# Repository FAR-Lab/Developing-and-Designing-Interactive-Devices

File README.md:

# Interactive-Device-Design
The main repository for the IDD class given by Wendy Ju in the Fall term of 2023 at Cornell Tech.

## Syllabus
[Syllabus](https://canvas.cornell.edu/courses/56846/assignments/syllabus)

## Class Discussion
Class discussion will occur on the [Cornell Tech Slack](https://cornelltech.slack.com), in the channel #idd-fall23

## Lectures
Lecture slides will be posted on Canvas.

## Labs
Labs will be updated on the [Interactive Lab Hub](https://github.com/FAR-Lab/Interactive-Lab-Hub) as announced on Slack or during the class (typically on Tuesdays). You will need to pull lab updates each week to get the new lab code and materials.

## Final Project

[Final Project](https://github.com/FAR-Lab/Developing-and-Designing-Interactive-Devices/blob/2023Fall/FinalProject.md)

## Student Submissions:

Fork  [the Interactive Lab Page repository](https://github.com/FAR-Lab/Interactive-Lab-Hub); detailed instructions for creating your lab hub and updating your labs are [here](https://github.com/FAR-Lab/Developing-and-Designing-Interactive-Devices/blob/2023Fall/readings/Submitting%20Labs.md).

When submitting your assignments, you will update your assignments on your own class lab hub, and post a link to your Github page on Canvas. Graders will review the assignments after the due date. Late assignments (e.g. your assignment is missing/incomplete at our grading time, which is after the due date) will be penalized by one letter grade per day late.

## Office Hours 

The main time to talk to the teaching team about your labs or projects are during the Thursday labs. 

Outside of that time, Professor Ju is generally available on Slack, and usually respond within hours during their working day, and by the next working day otherwise. 

The TAs office hours will be on Fridays.

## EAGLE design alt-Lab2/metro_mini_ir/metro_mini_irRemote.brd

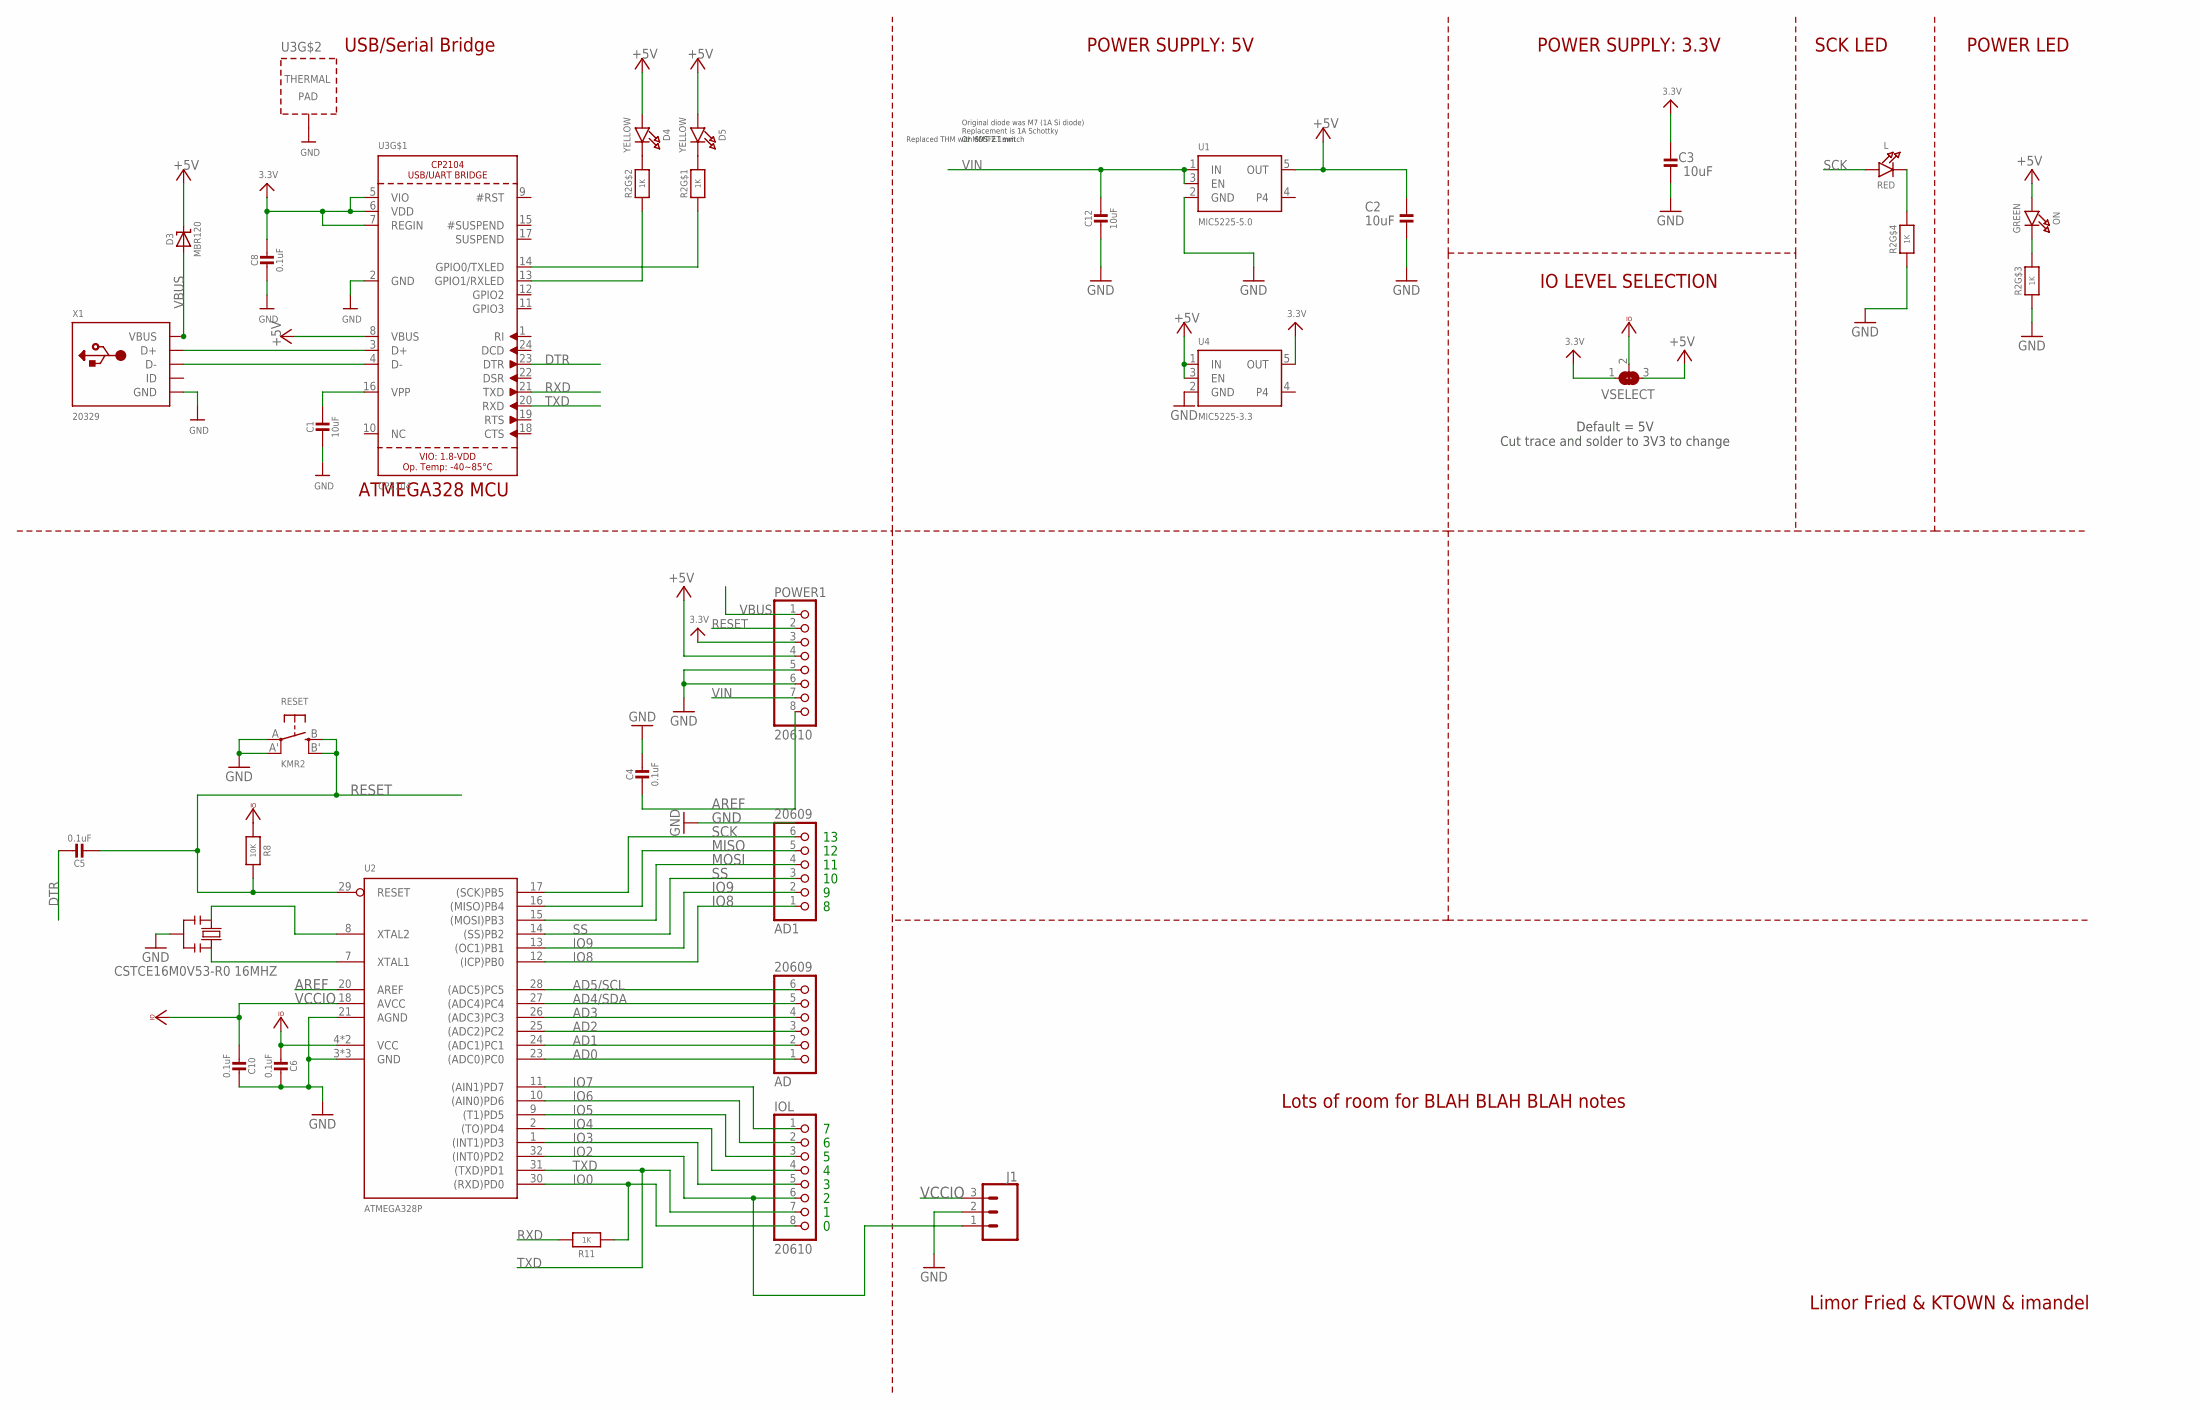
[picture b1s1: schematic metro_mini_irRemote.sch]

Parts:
AD, AD1: 20609; 1X06_ROUND
C1, C2, C3, C12: 10uF; 0805-NO
C4, C6, C8, C10: 0.1uF; 0805-NO
C5: 0.1uF; _0805MP
D3: MBR120; SOD-123
D4, D5: YELLOW; CHIPLED_0805_NOOUTLINE
IOL: 20610; 1X08_ROUND
J1: CONN_03; 1X03
L: RED; CHIPLED_0805_NOOUTLINE
ON: GREEN; CHIPLED_0805_NOOUTLINE
POWER1: 20610; 1X08_ROUND_70
R2: 1K; RESPACK_4X0603
R8: 10K; 0805-NO
R11: 1K; 0805-NO
RESET: KMR2; BTN_KMR2_4.6X2.8
U1: MIC5225-5.0; SOT23-5
U2: ATMEGA328P; MLF32-TH
U3: CP2104; QFN24_4MM_SMSC
U4: MIC5225-3.3; SOT23-5
VSELECT: SOLDERJUMPER_2WAY; SOLDERJUMPER_2WAY_OPEN_NOPASTE
X1: 20329; 4UCONN_20329_V2
Y2: CSTCE16M0V53-R0 16MHZ; RESONATOR

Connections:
3.3V: C3.2, C8.1, POWER1.3, U3.5 (VIO), U3.6 (VDD), U3.7 (REGIN), U4.5 (OUT), VSELECT.1
+5V: C2.2, D3.C, D4.A, D5.A, ON.A, POWER1.4, U1.5 (OUT), U3.8 (VBUS), U4.1 (IN), U4.3 (EN), VSELECT.3
AD0: AD.1, U2.23 ((ADC0)PC0)
AD1: AD.2, U2.24 ((ADC1)PC1)
AD2: AD.3, U2.25 ((ADC2)PC2)
AD3: AD.4, U2.26 ((ADC3)PC3)
AD4/SDA: AD.5, U2.27 ((ADC4)PC4)
AD5/SCL: AD.6, U2.28 ((ADC5)PC5)
AREF: C4.2, POWER1.8, U2.20 (AREF)
DTR: C5.1, U3.23 (DTR)
GND: C1.2, C2.1, C3.1, C4.1, C6.1, C8.2, C10.1, C12.2, J1.2, POWER1.5, POWER1.6, R2.3 (1), R2.4 (1), RESET.A, RESET.A' (P1), U1.2 (GND), U2.3 (GND), U2.5 (GND), U2.21 (AGND), U2.TH (GND), U3.2 (GND), U3.THERM (TP), U4.2 (GND), X1.BASE@1 (GND), X1.BASE@2 (GND), X1.GND, X1.SPRT@1 (GND), X1.SPRT@2 (GND), X1.SPRT@3 (GND), X1.SPRT@4 (GND), Y2.2
IO0: IOL.8, R11.1, U2.30 ((RXD)PD0)
IO2: IOL.6, J1.1, U2.32 ((INT0)PD2)
IO3: IOL.5, U2.1 ((INT1)PD3)
IO4: IOL.4, U2.2 ((TO)PD4)
IO5: IOL.3, U2.9 ((T1)PD5)
IO6: IOL.2, U2.10 ((AIN0)PD6)
IO7: IOL.1, U2.11 ((AIN1)PD7)
IO8: AD1.1, U2.12 ((ICP)PB0)
IO9: AD1.2, U2.13 ((OC1)PB1)
MISO: AD1.5, U2.16 ((MISO)PB4)
MOSI: AD1.4, U2.15 ((MOSI)PB3)
unnamed: L.C, R2.5 (2)
unnamed: ON.C, R2.6 (2)
unnamed: R2.1, U3.14 (GPIO0/TXLED)
unnamed: D4.C, R2.7 (2)
unnamed: D5.C, R2.8 (2)
unnamed: U3.3 (D+), X1.D+
unnamed: U3.4 (D-), X1.D-
unnamed: C1.1, U3.16 (VPP)
unnamed: R2.2 (1), U3.13 (GPIO1/RXLED)
RESET: C5.2, POWER1.2, R8.1, RESET.B (S), RESET.B' (S1), U2.29 (RESET)
RXD: R11.2, U3.21 (TXD)
SCK: AD1.6, L.A, U2.17 ((SCK)PB5)
SS: AD1.3, U2.14 ((SS)PB2)
TXD: IOL.7, U2.31 ((TXD)PD1), U3.20 (RXD)
VBUS: D3.A, POWER1.1, X1.VBUS
VCCIO: C6.2, C10.2, J1.3, R8.2, U2.4 (VCC), U2.6 (VCC), U2.18 (AVCC), VSELECT.2
VIN: C12.1, POWER1.7, U1.1 (IN), U1.3 (EN)
XTAL1: U2.7 (XTAL1), Y2.3
XTAL2: U2.8 (XTAL2), Y2.1

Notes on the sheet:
Limor Fried & KTOWN & imandel
Original diode was M7 (1A Si diode) Replacement is 1A Schottky Or MOSFET switch
Replaced THM with SMT 2.1mm
POWER SUPPLY: 5V
USB/Serial Bridge
POWER SUPPLY: 3.3V
IO LEVEL SELECTION
POWER LED
ATMEGA328 MCU
SCK LED
Lots of room for BLAH BLAH BLAH notes
Default = 5V Cut trace and solder to 3V3 to change

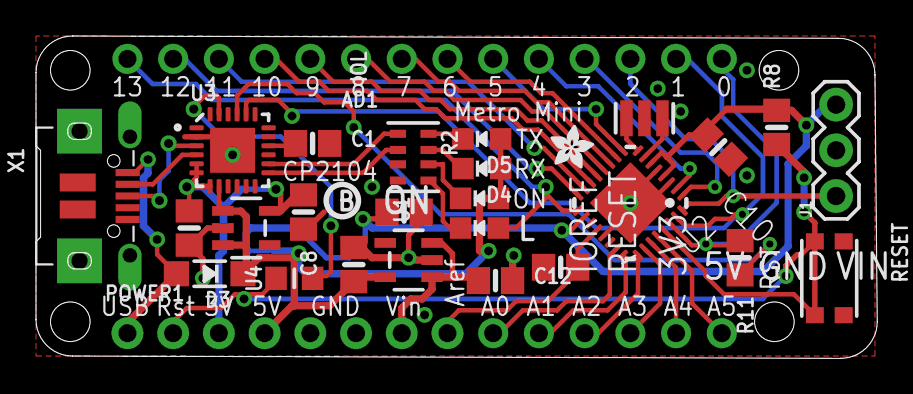
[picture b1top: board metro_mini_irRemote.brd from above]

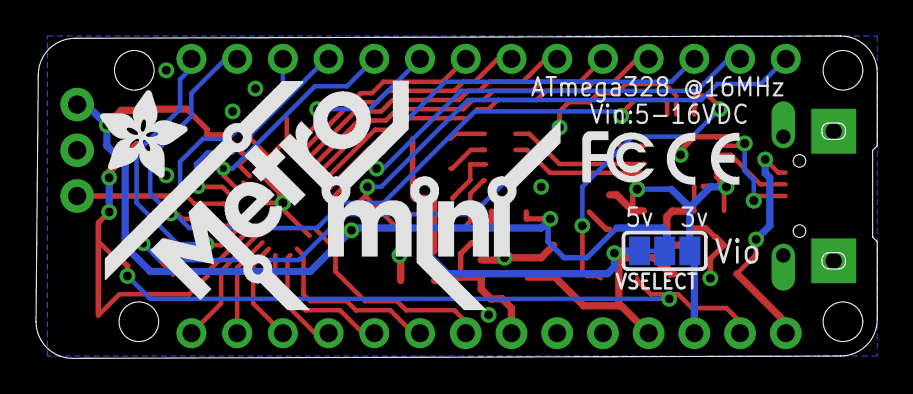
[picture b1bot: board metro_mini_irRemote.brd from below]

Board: 2 copper layers, 46.7 x 17.9 mm, 36 parts (5 on the bottom side), 41 nets.

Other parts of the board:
U$4: PCBFEAT-REV-040
U$5: ADAFRUIT_2.5MM
U$7: METROMINI_SILK
U$10: ADAFRUIT_5MM
U$12: SYMBOL_CE_TINY
U$14: SYMBOL_FCC_TINY

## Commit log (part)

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2019-09-04 Update hi.
2019-09-04 Rename hi. to hi.md
2019-09-08 Added my link to readme
2019-09-08 Adding ReadMe to ckshei
2019-09-09 Add Lab hub link for Bo Fang (bf366)
2019-09-09 Adding link to assignment page
2019-09-10 Update README.md
    added WJL hub link with Lab 01 submission link
    also corrected numbering order in names list
2019-09-10 add Fei Gao
2019-09-10 Added Eduardo Casitllo (ec833) Lab 1 Submission
2019-09-10 Adding link to my github page
2019-09-11 Orientation Image
2019-09-18 Natalie's lecture
2019-09-25 added box with hinge
2019-09-26 Diagram for assembling the box
2019-10-01 Update README.md
    Dropped class
2019-10-10 Create Readings
2019-11-06 Adding final project repo link
2019-11-09 Add files via upload
    Noam Zomerfeld’s slides from his 11/5 guest lecture!
2019-11-12 Adding final Project link
2019-11-12 Add Zwee Dao's final project: self-balancing robot
2019-11-25 Noah slides added
2019-11-26 added davids slides, and GitIgnore
2019-11-26 Syllabus Updated
2020-01-31 Create Proximity Sensor
2020-01-31 Create Raspberry Pi Trouble Shooting
2020-09-02 DEMO
    DEMO
2020-09-02 Create lab1 - demo
2020-09-02 Create TESTING
2020-09-02 Create TEST_DOC
2020-09-03 testing
2020-09-07 altlab2
2020-09-07 pages
2020-09-07 renamed
2020-09-07 Bump websocket-extensions from 0.1.3 to 0.1.4 in /presentations/altlab2
    Bumps [websocket-extensions](https://github.com/faye/websocket-extensions-node) from 0.1.3 to 0.1.4.
    - [Release notes](https://github.com/faye/websocket-extensions-node/releases)
    - [Changelog](https://github.com/faye/websocket-extensions-node/blob/master/CHANGELOG.md)
    - [Commits](https://github.com/faye/websocket-extensions-node/compare/0.1.3...0.1.4)
2020-09-07 Bump lodash from 4.17.15 to 4.17.20 in /presentations/altlab2
    Bumps [lodash](https://github.com/lodash/lodash) from 4.17.15 to 4.17.20.
    - [Release notes](https://github.com/lodash/lodash/releases)
    - [Commits](https://github.com/lodash/lodash/compare/4.17.15...4.17.20)
2020-09-08 added boards;
2020-09-11 oved slides
2020-09-11 deleted old presentation
2020-09-11 deleted dist
2020-10-20 Add files via upload
    "Hello world" on remote browser for LAB7 ( basicserver.py )
2020-10-21 Add files via upload
    After button press to "light"
2020-10-21 Add files via upload
    Interacting with arduino and rpi
2021-02-09 Bump highlight.js from 10.0.3 to 10.4.1 in /Slides/altlab2
    Bumps [highlight.js](https://github.com/highlightjs/highlight.js) from 10.0.3 to 10.4.1.
    - [Release notes](https://github.com/highlightjs/highlight.js/releases)
    - [Changelog](https://github.com/highlightjs/highlight.js/blob/master/CHANGES.md)
    - [Commits](https://github.com/highlightjs/highlight.js/compare/10.0.3...10.4.1)
2021-02-09 Bump ini from 1.3.5 to 1.3.8 in /Slides/altlab2
    Bumps [ini](https://github.com/isaacs/ini) from 1.3.5 to 1.3.8.
    - [Release notes](https://github.com/isaacs/ini/releases)
    - [Commits](https://github.com/isaacs/ini/compare/v1.3.5...v1.3.8)
2021-02-09 Bump lodash from 4.17.15 to 4.17.20 in /Slides/altlab2
    Bumps [lodash](https://github.com/lodash/lodash) from 4.17.15 to 4.17.20.
    - [Release notes](https://github.com/lodash/lodash/releases)
    - [Commits](https://github.com/lodash/lodash/compare/4.17.15...4.17.20)
2021-02-09 Bump websocket-extensions from 0.1.3 to 0.1.4 in /Slides/altlab2
    Bumps [websocket-extensions](https://github.com/faye/websocket-extensions-node) from 0.1.3 to 0.1.4.
    - [Release notes](https://github.com/faye/websocket-extensions-node/releases)
    - [Changelog](https://github.com/faye/websocket-extensions-node/blob/master/CHANGELOG.md)
    - [Commits](https://github.com/faye/websocket-extensions-node/compare/0.1.3...0.1.4)
2021-02-09 cleaned files for Spring 2021
    cleaned files for Spring 2021
2021-02-09 re-create submitting Labs with Github
2021-02-09 resurrecting instructions for github lab hub
2021-02-10 Added student link
2021-02-10 added names
2021-02-15 Update README.md
    Add submission link
2021-08-24 Updated Instrructions
2021-08-30 Updated lab list and link
2021-08-30 Updated Slack link
2021-09-02 readme: added jns223 repo to repo list
2021-09-02 Add repo link for yp432
2021-09-14 Update Lab 2 link
2021-10-12 Link to Lab 4
2021-11-02 Create FinalProject
2023-11-28 Update FinalProject.md (Due Dates)

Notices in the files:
parts and their libraries:
microbuilder: This work is placed in the public domain, and may be freely used for commercial and non-commercial work with the following conditions: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
SparkFun-Connectors: Licensing: Creative Commons ShareAlike 4.0 International - https://creativecommons.org/licenses/by-sa/4.0
